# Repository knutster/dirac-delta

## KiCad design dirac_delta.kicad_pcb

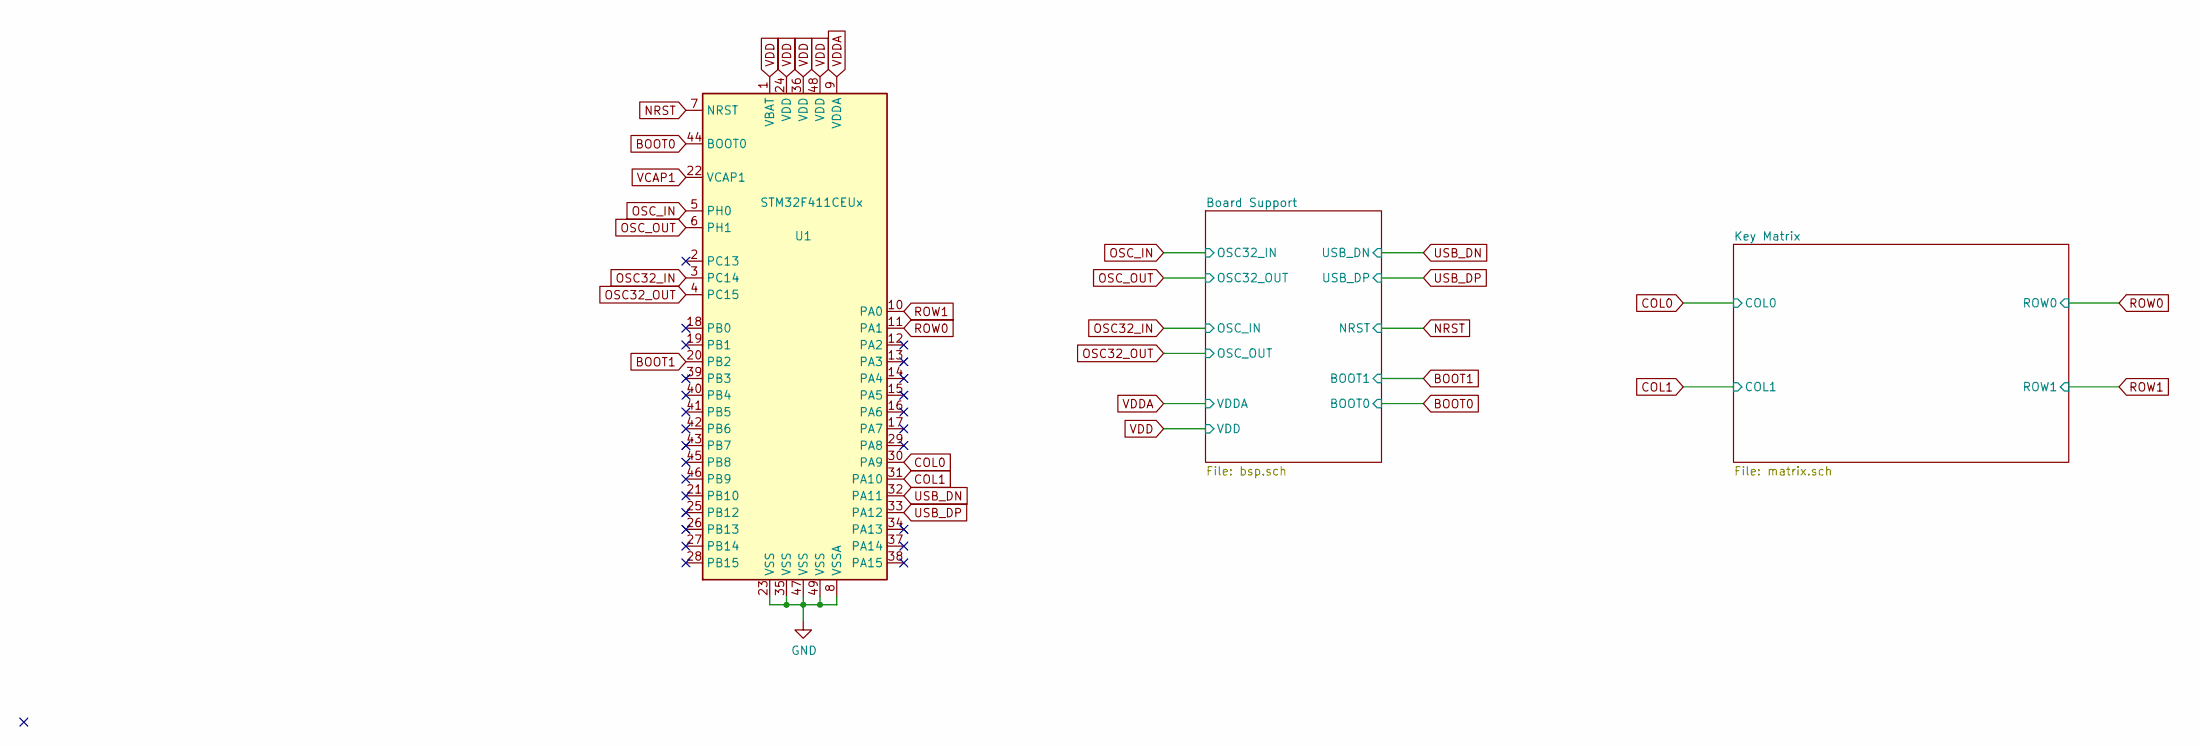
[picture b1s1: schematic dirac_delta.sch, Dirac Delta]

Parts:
U1: STM32F411CEUx; QFN-48-1EP_7x7mm_P0.5mm_EP5.6x5.6mm

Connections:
BOOT0: U1.44 (BOOT0); also elsewhere on the board
BOOT1: U1.20 (PB2); also elsewhere on the board
COL0: U1.30 (PA9); also elsewhere on the board
COL1: U1.31 (PA10); also elsewhere on the board
GND: U1.8 (VSSA), U1.23 (VSS), U1.35 (VSS), U1.47 (VSS), U1.49 (VSS); also elsewhere on the board
NRST: U1.7 (NRST); also elsewhere on the board
OSC32_IN: U1.3 (PC14); also elsewhere on the board
OSC32_OUT: U1.4 (PC15); also elsewhere on the board
OSC_IN: U1.5 (PH0); also elsewhere on the board
OSC_OUT: U1.6 (PH1); also elsewhere on the board
ROW0: U1.11 (PA1); also elsewhere on the board
ROW1: U1.10 (PA0); also elsewhere on the board
USB_DN: U1.32 (PA11); also elsewhere on the board
USB_DP: U1.33 (PA12); also elsewhere on the board
VDD: U1.1 (VBAT), U1.24 (VDD), U1.36 (VDD), U1.48 (VDD); also elsewhere on the board
VDDA: U1.9 (VDDA); also elsewhere on the board

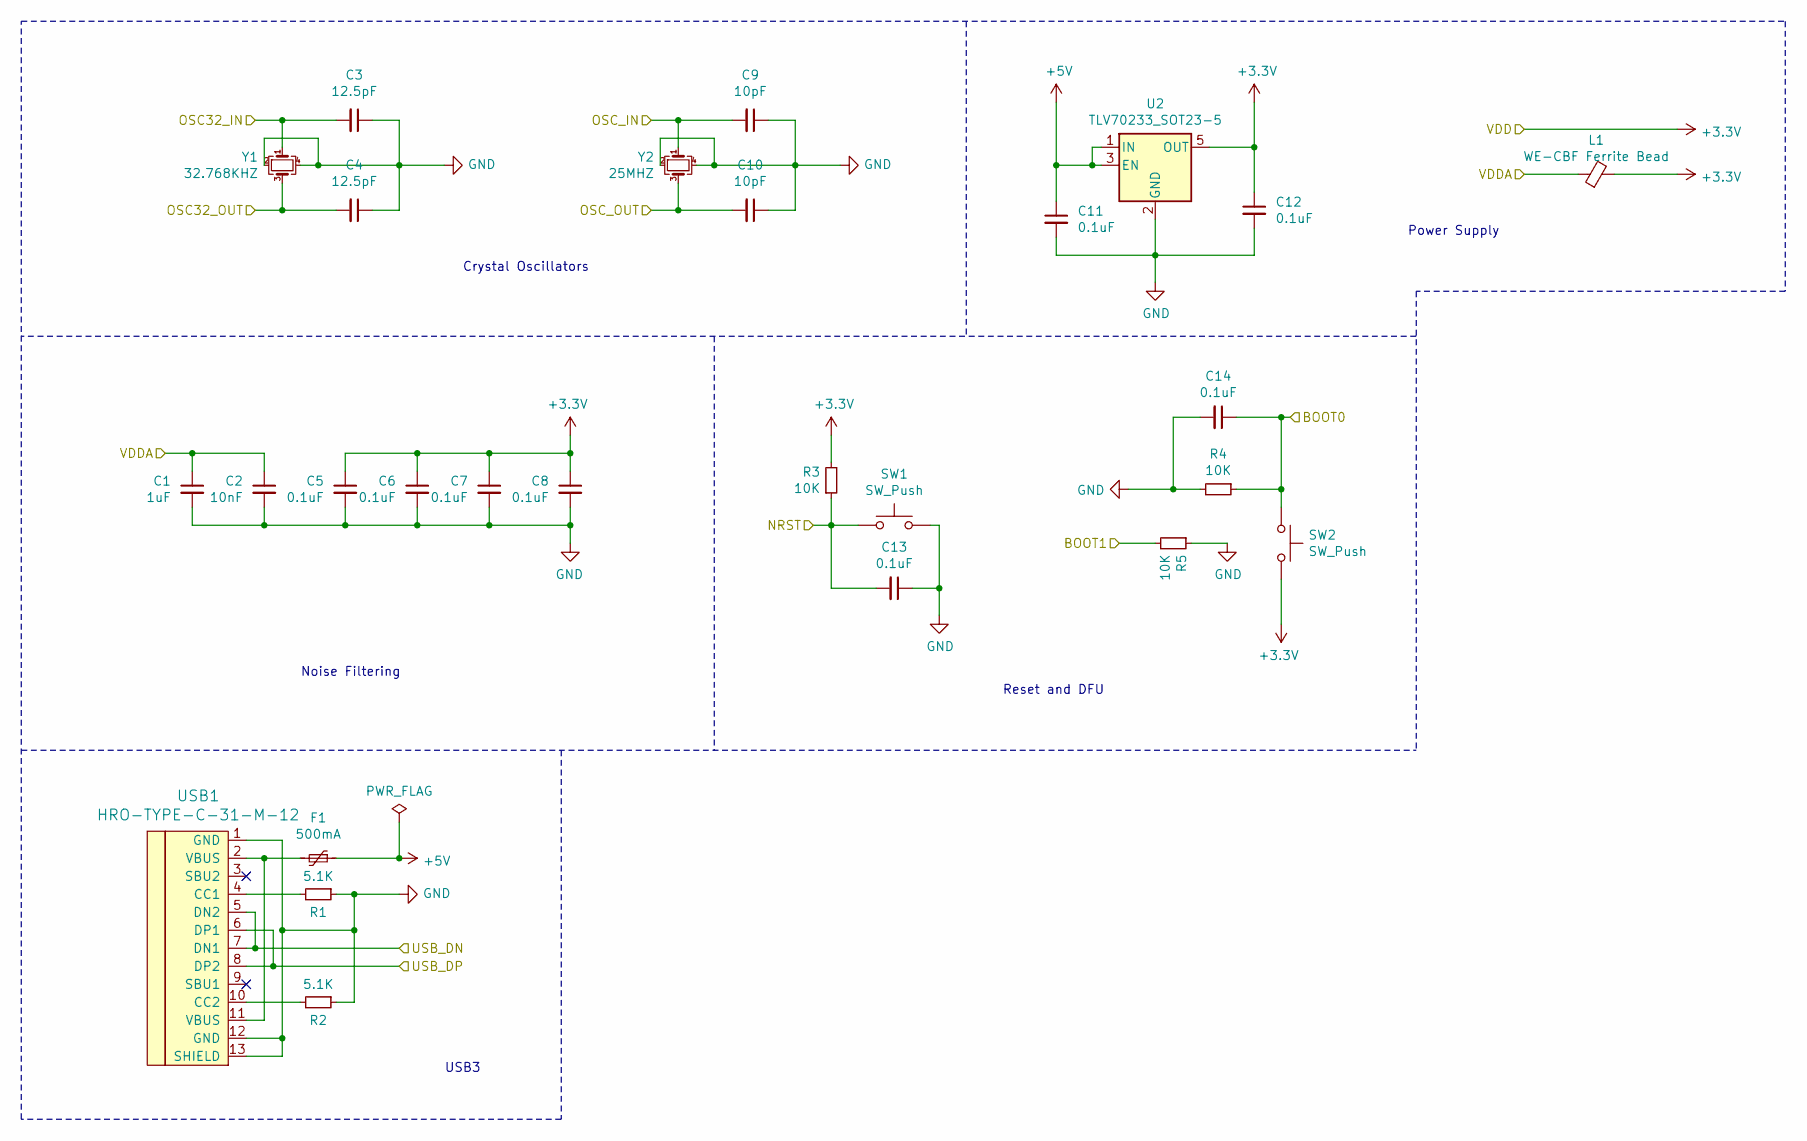
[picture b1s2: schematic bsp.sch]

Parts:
C1: 1uF; C_0805_2012Metric
C2: 10nF; C_0805_2012Metric
C3, C4: 12.5pF; C_0805_2012Metric
C5, C6, C7, C8, C11, C12, C13, C14: 0.1uF; C_0805_2012Metric
C9, C10: 10pF; C_0805_2012Metric
F1: 500mA; Fuse_1206_3216Metric
L1: WE-CBF Ferrite Bead; L_0805_2012Metric
R1, R2: 5.1K; R_0805_2012Metric
R3, R4, R5: 10K; R_0805_2012Metric
SW1, SW2: SW_Push; SKQG-1155865
U2: TLV70233_SOT23-5; SOT-23-5
USB1: HRO-TYPE-C-31-M-12
Y1: 32.768KHZ; Crystal_SMD_3225-4Pin_3.2x2.5mm
Y2: 25MHZ; Crystal_SMD_3225-4Pin_3.2x2.5mm

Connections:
+5V: C11.1, F1.1, U2.1 (IN), U2.3 (EN)
BOOT0: C14.1, R4.1, SW2.1; also elsewhere on the board
BOOT1: R5.2; also elsewhere on the board
GND: C1.2, C2.2, C3.1, C4.1, C5.2, C6.2, C7.2, C8.2, C9.1, C10.1, C11.2, C12.2, C13.1, C14.2, R1.1, R2.1, R4.2, R5.1, SW1.2, U2.2 (GND), USB1.1 (GND), USB1.12 (GND), USB1.13 (SHIELD), Y1.2, Y1.4, Y2.2, Y2.4; also elsewhere on the board
NRST: C13.2, R3.1, SW1.1; also elsewhere on the board
unnamed: F1.2, USB1.2 (VBUS), USB1.11 (VBUS)
unnamed: R1.2, USB1.4 (CC1)
unnamed: R2.2, USB1.10 (CC2)
OSC32_IN: C9.2, Y2.1; also elsewhere on the board
OSC32_OUT: C10.2, Y2.3; also elsewhere on the board
OSC_IN: C3.2, Y1.1; also elsewhere on the board
OSC_OUT: C4.2, Y1.3; also elsewhere on the board
USB_DN: USB1.5 (DN2), USB1.7 (DN1); also elsewhere on the board
USB_DP: USB1.6 (DP1), USB1.8 (DP2); also elsewhere on the board
VDD: C5.1, C6.1, C7.1, C8.1, C12.1, L1.2, R3.2, SW2.2, U2.5 (OUT); also elsewhere on the board
VDDA: C1.1, C2.1, L1.1; also elsewhere on the board

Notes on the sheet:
Crystal Oscillators
Noise Filtering
Reset and DFU
Power Supply
USB3

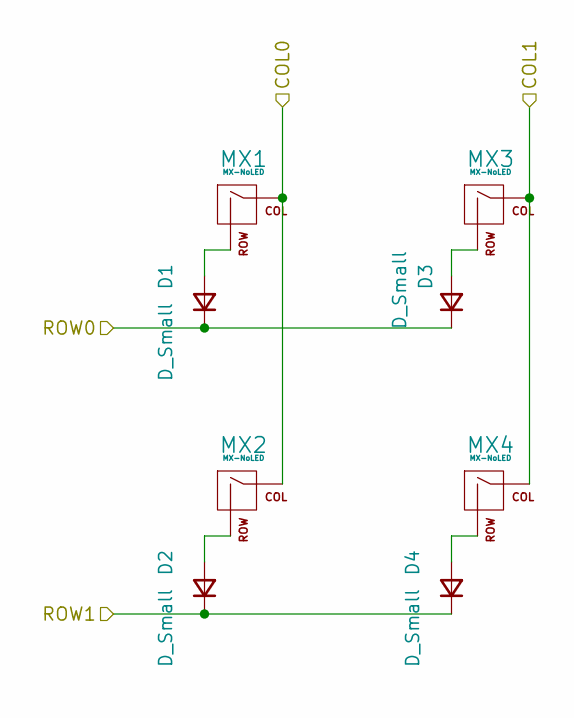
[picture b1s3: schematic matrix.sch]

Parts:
D1, D2, D3, D4: D_Small; D_SOD-123
MX1, MX2, MX3, MX4: MX-NoLED; MXOnly-1U-Hotswap

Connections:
COL0: MX1.1 (COL), MX2.1 (COL); also elsewhere on the board
COL1: MX3.1 (COL), MX4.1 (COL); also elsewhere on the board
unnamed: D1.2 (A), MX1.2 (ROW)
unnamed: D2.2 (A), MX2.2 (ROW)
unnamed: D3.2 (A), MX3.2 (ROW)
unnamed: D4.2 (A), MX4.2 (ROW)
ROW0: D1.1 (K), D3.1 (K); also elsewhere on the board
ROW1: D2.1 (K), D4.1 (K); also elsewhere on the board

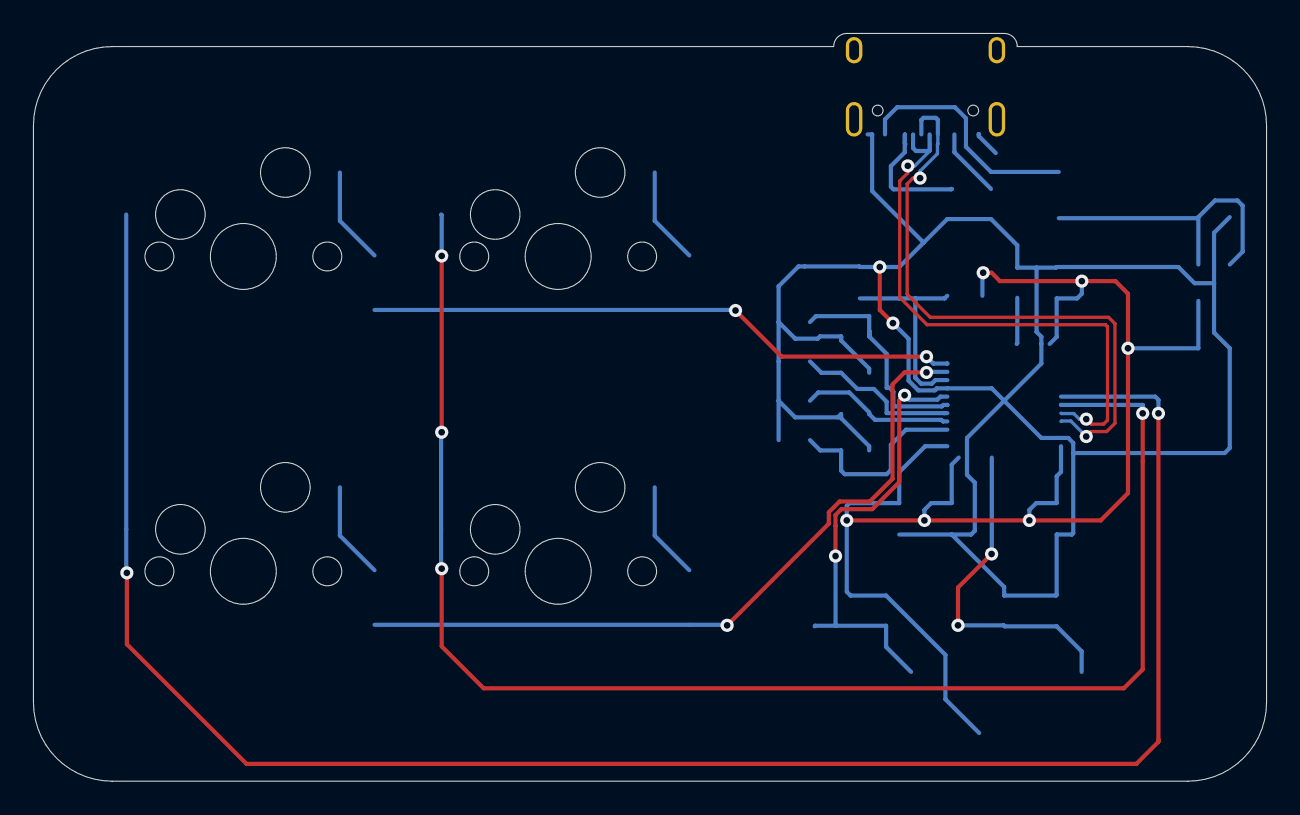
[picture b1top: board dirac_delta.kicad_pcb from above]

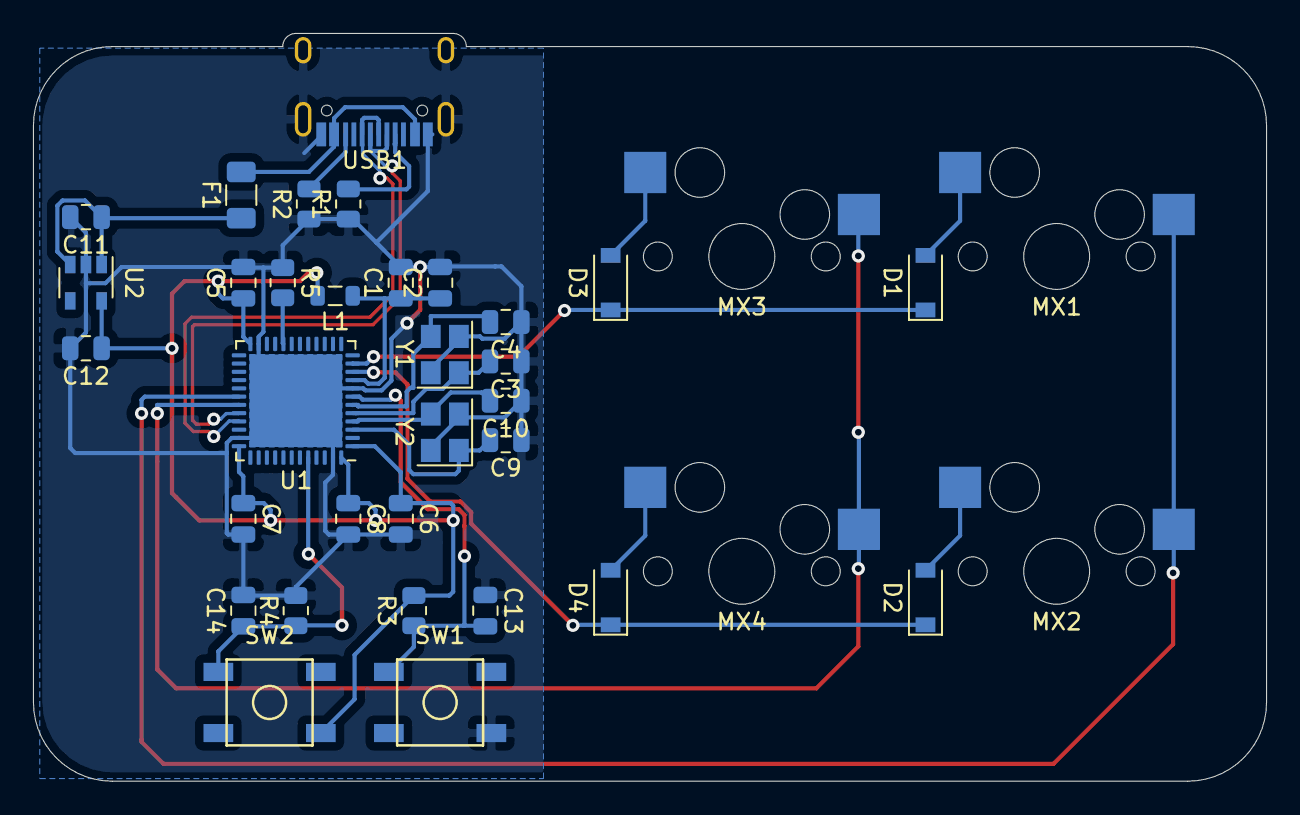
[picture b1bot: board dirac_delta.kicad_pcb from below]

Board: 2 copper layers, 74.6 x 45.2 mm, 36 parts (32 on the bottom side), 24 nets.

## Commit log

2021-05-15 Added libraries
2021-05-15 Added library locations
2021-05-15 Added BSP
2021-05-18 Added Gerbers
